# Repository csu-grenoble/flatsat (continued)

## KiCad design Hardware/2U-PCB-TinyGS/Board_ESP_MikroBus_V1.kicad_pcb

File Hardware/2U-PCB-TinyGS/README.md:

# INISAT Board for TinyGS 2.4GHz Station

This board is the firts version of the [LoRa 2.4GHz gateway](https://github.com/thingsat/tinygs_2g4station) for [TinyGS](https://tinygs.com/).

Contain Schematic and PCB file for ESP32 Vroom + 2 Mikrobus modules + 2 groves connectors (RXTX,I2C).

This Board is designed to support a ESP32 devkitC-V4 and 2 MiKroBus modules. This board is the firts version of the 2.4GHz tinygs ground station gateway and named Board_V2

The purpose of this board is to control mikrobus modules including SX1280 technology that will transmit and receive messages on a 2.4GHz radio frequency. Each module are connected to a ESP32 which will be connected to the wifi.

Mikrobus board is an add-on board socket standard made by [mikroe](https://www.mikroe.com/mikrobus)

## Pinout

Connection between ESP32 - ESP32-DevKitC V4 and Mikrobus modules

MiKroBus 0:
	 				 
	SPI_0:
	CLK 	IO18
	MISO	IO19
	MOSI	IO23
	NSS(CS)	IO05
	
	UART_0	:
	Tx	NC
	Rx	NC
	
	I2C:
	SDA	IO21
	SCL	IO22
	
	AN_0	IO33
	RESET_0 IO32
	PWM_0	IO25
	INT_0	IO26

MiKroBus 1: 				 
	
	SPI_0
	CLK 	IO18
	MISO	IO19
	MOSI	IO23
	NSS 	IO15
	
	UART_2
	Tx	IO17
	Rx	IO16
	
	I2C:
	SDA	IO21
	SCL	IO22
	
	AN_1	IO27
	RESET_1 IO14
	PWM_1	IO04
	INT_1	IO13

Grove connector available on board :

	I2C:			UART_2(Rx/Tx):		GPIO(INPUT Only):
	SDA   IO21		Tx	IO17		IO34
	SCL   IO22		Rx	IO16		IO35

UART_2 can be connected to module MiKroBus 2 or to grove connector. A jumper need to be plug to choose beetween grove output or the mikrobus module.

Two UFL connected to a SMA mount edge connector are available to plug an antenna. They are disconnected from the rest of the board, which allows to connect the module that you want to the antenna, with a SMA -UFL connector.

A powerbank can be plug under the board to supply the 3V. The [powerbank](https://www.amazon.com/Diymore-Lithium-Battery-Charging-Arduino/dp/B07SZKNST4) is design for ESP32 and is purchasable on amazon. 
5V is only available on the Mikrobus 1 module. 

Careful:
* UART0 is used for flashing and debuging. Be very careful to its use.
* GPIO grove connector are INPUT only, ESP32wroom cannot write on this connection.
* Both Chip selec (NSS) for the SPI communication are Pulled HIGH (IO05 & IO15).
* No 5V on Mikrobus 0. 

## Library and footprint

Lib & empreinte folder contains all necessary symbol and footprint for the project:
* ESP32 symbol and footprint. Footprint has been changed to match with our ESP32-devkitC-V4
* Mikrobus (mikroe-2439) symbol and footprint
* Grove connector for I2C and RxTx connection
* SMA and UFL connector

## Files

* .pro: File containing the parameters of the project.
* .sch: Schema files.
* .kicad_pcb: Printed circuit board files.
* sym-info-cache: Library list file (symbol library table): declaration of component symbol libraries available for the schema editor.
* fp-lib-table: Library list file (footprint library table): declaration of component footprint libraries available for the PCB editor.

## Contributors

* Didier DONSEZ
* [Samuel Barnola](https://www.linkedin.com/in/samuel-barnola-816354281/) ([initial design](https://github.com/thingsat/tinygs_2g4station))
* [Lucas ORLANDO BERNARDES](https://www.linkedin.com/in/lucas-orlando-bernardes-1b7397256/)

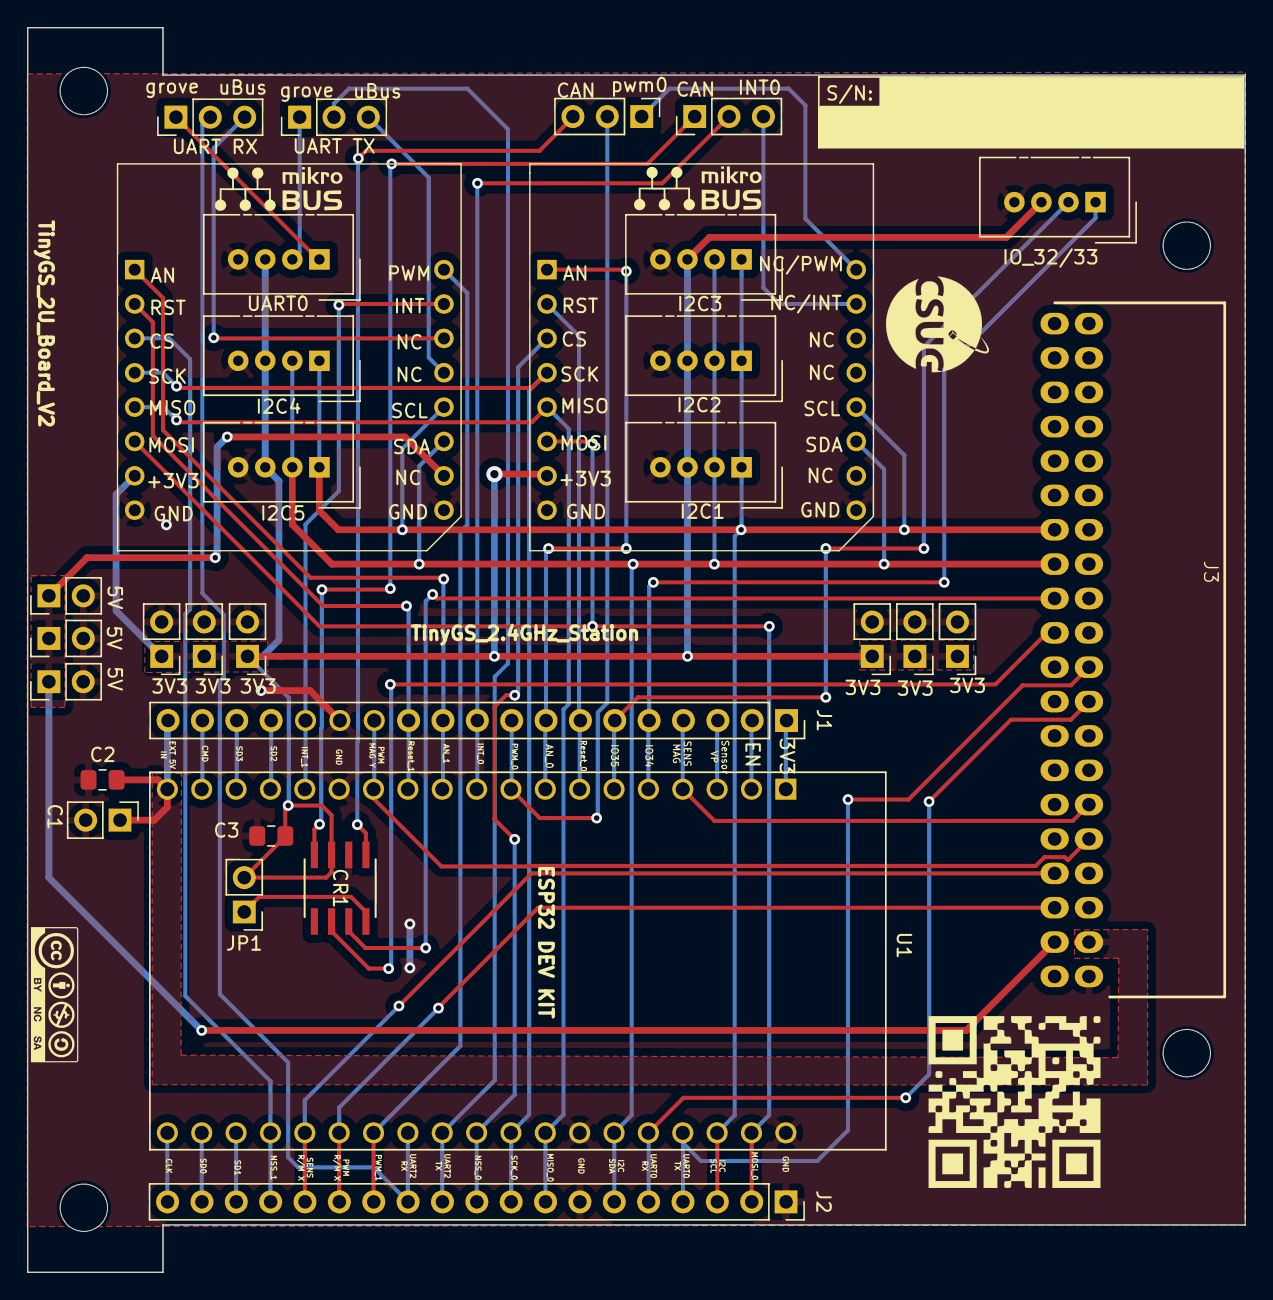
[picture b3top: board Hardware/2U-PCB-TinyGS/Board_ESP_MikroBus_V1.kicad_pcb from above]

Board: 2 copper layers, 90.0 x 92.0 mm, 31 parts (0 on the bottom side), 49 nets.

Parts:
3.1, 3.2, 3.3, 3.4, 3.5, 3.6, 5V1, 5V2, 5V3: Conn_01x02; PinHeader_1x02_P2.54mm_Vertical
C1: C; PinHeader_1x02_P2.54mm_Vertical
C2: C; C_0805_2012Metric_Pad1.18x1.45mm_HandSolder
C3: 100nF; C_0805_2012Metric_Pad1.18x1.45mm_HandSolder
CR1: L9616; SO-8_STM
I2C1, I2C2, I2C3, I2C4, I2C5: Grove; NS-Tech_Grove_1x04_P2mm_Vertical
IO_32/33: Grove; NS-Tech_Grove_1x04_P2mm_Vertical
J1, J2: Conn_01x19; PinSocket_1x19_P2.54mm_Vertical
J3: Bus Standard; flatsat_conn
JP1: Jumper_2_Open; PinHeader_1x02_P2.54mm_Vertical
Jmp_Rx1, Jmp_Rx2: Jumper_NC_Dual; PinHeader_1x03_P2.54mm_Vertical
Jmp_Tx1, Jmp_Tx2: Jumper_NC_Dual; PinHeader_1x03_P2.54mm_Vertical
MiKroBus_0, MiKroBus_1: MIKROE-924; MIKROE924
U1: ESP32-DEVKITC-32D; MODULE_ESP32-DEVKITC-32D
UART0: Grove; NS-Tech_Grove_1x04_P2mm_Vertical

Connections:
+3.3V: 3.1.1, 3.2.1, 3.3.1, 3.4.1, 3.5.1, 3.6.1, C3.1, CR1.3 (VS), I2C1.3, I2C2.3, I2C3.3, I2C4.3, I2C5.3, IO_32/33.3, J3.2 (3V3), JP1.2 (B), MiKroBus_0.7 (+3.3V), MiKroBus_1.7 (+3.3V), UART0.3
+5V: 5V1.1, 5V2.1, 5V3.1, J3.4 (5V), MiKroBus_1.15 (+5V)
/1: J1.1, U1.1 (3V3)
/2: J1.2, U1.2 (EN)
/3: J1.3, U1.3 (SENSOR_VP)
/4: J1.4, J3.11 (NC), U1.4 (SENSOR_VN)
/13: J1.13, J3.9 (NC4), U1.13 (IO12)
/16: J1.16, U1.16 (SD2)
/17: J1.17, U1.17 (SD3)
/18: J1.18, U1.18 (CMD)
/19: C1.1, C2.1, J1.19, J3.3 (V_IN), U1.19 (EXT_5V)
/33: J2.14, J3.6 (NC1), U1.33 (IO0)
/34: J2.15, J3.8 (NC3), U1.34 (IO2)
/36: J2.17, U1.36 (SD1)
/37: J2.18, U1.37 (SD0)
/38: J2.19, U1.38 (CLK)
AN_0: J1.8, MiKroBus_0.1 (AN), U1.8 (IO33)
AN_1: J1.11, MiKroBus_1.1 (AN), U1.11 (IO27)
CAN0_RD: CR1.4 (RX0), Jmp_Rx2.1
CAN0_TD: CR1.1 (TX0), Jmp_Tx2.3
CAN_RD: CR1.6 (C_L), J3.22 (RD)
CAN_TD: CR1.7 (C_H), J3.24 (TD)
ESP_CAN0_RD/INT_0: J1.10, Jmp_Rx2.2, U1.10 (IO26)
ESP_CAN0_TD/PWM_0: J1.9, Jmp_Tx2.2, U1.9 (IO25)
GNDREF: 3.1.2, 3.2.2, 3.3.2, 3.4.2, 3.5.2, 3.6.2, 5V1.2, 5V2.2, 5V3.2, C1.2, C2.2, C3.2, CR1.2 (GND), I2C1.4, I2C2.4, I2C3.4, I2C4.4, I2C5.4, IO_32/33.4, J1.14, J2.1, J2.7, J3.1 (GND), MiKroBus_0.8 (GND_1), MiKroBus_0.16 (GND_2), MiKroBus_1.8 (GND_1), MiKroBus_1.16 (GND_2), U1.14 (GND1), U1.20 (GND3), U1.26 (GND2), UART0.4
I2C_SCL: I2C1.1, I2C2.1, I2C3.1, I2C4.1, I2C5.1, J2.3, J3.28 (SCL/TX), MiKroBus_0.13 (SCL), MiKroBus_1.13 (SCL), U1.22 (IO22)
I2C_SDA: I2C1.2, I2C2.2, I2C3.2, I2C4.2, I2C5.2, J2.6, J3.26 (SDA/RX), MiKroBus_0.14 (SDA), MiKroBus_1.14 (SDA), U1.25 (IO21)
IN34: IO_32/33.1, J1.5, U1.5 (IO34)
IN35: IO_32/33.2, J1.6, U1.6 (IO35)
INT_0: Jmp_Rx2.3, MiKroBus_0.10 (INT)
INT_1: J1.15, MiKroBus_1.10 (INT), U1.15 (IO13)
MISO_0: J2.8, MiKroBus_0.5 (MISO), MiKroBus_1.5 (MISO), U1.27 (IO19)
MOSI_0: J2.2, MiKroBus_0.6 (MOSI), MiKroBus_1.6 (MOSI), U1.21 (IO23)
NSS_0: J2.10, MiKroBus_0.3 (CS), U1.29 (IO5)
NSS_1: J2.16, MiKroBus_1.3 (CS), U1.35 (IO15)
unnamed: CR1.8 (ASC), JP1.1 (A)
PWM_0: Jmp_Tx2.1, MiKroBus_0.9 (PWM)
PWM_1: J2.13, MiKroBus_1.9 (PWM), U1.32 (IO4)
Reset_0: J1.7, MiKroBus_0.2 (RST), U1.7 (IO32)
Reset_1: J1.12, MiKroBus_1.2 (RST), U1.12 (IO14)
SCK_0: J2.9, MiKroBus_0.4 (SCK), MiKroBus_1.4 (SCK), U1.28 (IO18)
UART0_Rx: J2.5, J3.17 (RX/SDA), U1.24 (RXD0)
UART0_Tx: J2.4, J3.19 (TX/SCL), U1.23 (TXD0)
UART2_Rx: J2.12, Jmp_Rx1.2, U1.31 (IO16)
UART2_Rx_MiKroBus: Jmp_Rx1.3, MiKroBus_1.11 (RX)
UART2_Rx_grove: Jmp_Rx1.1, UART0.1
UART2_Tx: J2.11, Jmp_Tx1.2, U1.30 (IO17)
UART2_Tx_MiKroBus: Jmp_Tx1.3, MiKroBus_1.12 (TX)
UART2_Tx_grove: Jmp_Tx1.1, UART0.2

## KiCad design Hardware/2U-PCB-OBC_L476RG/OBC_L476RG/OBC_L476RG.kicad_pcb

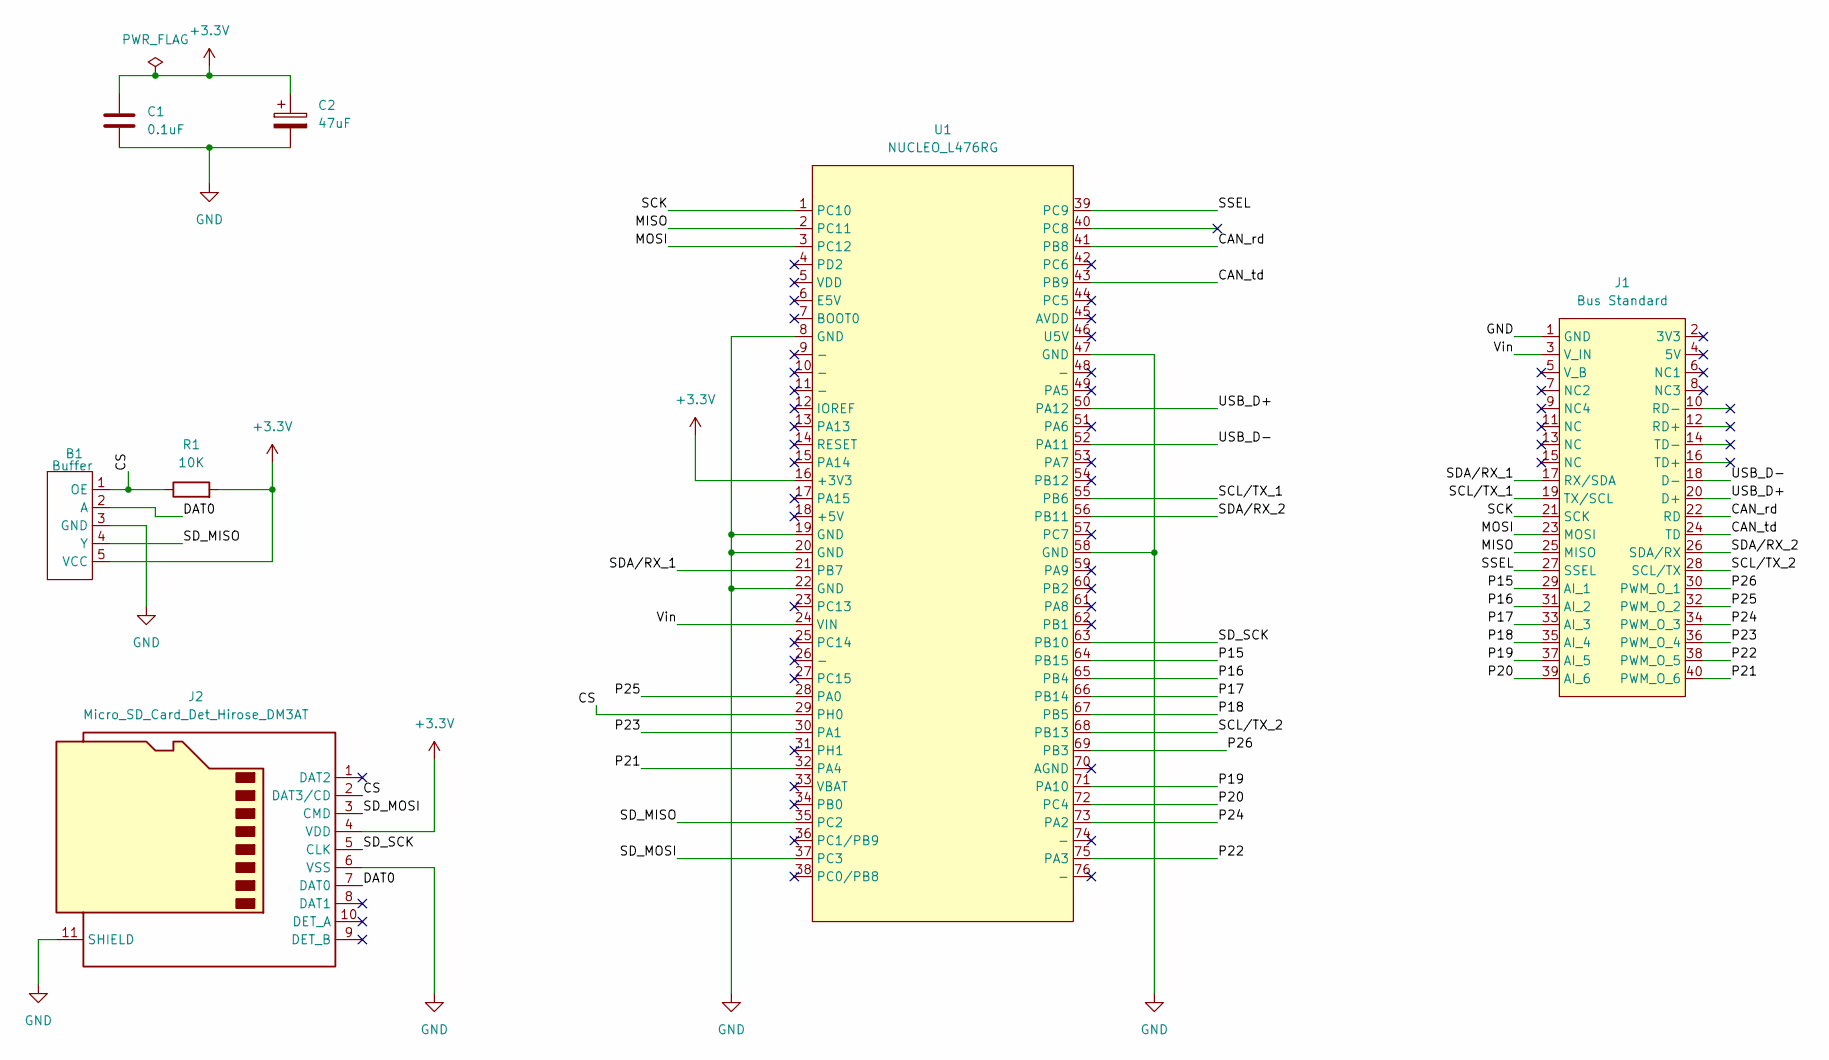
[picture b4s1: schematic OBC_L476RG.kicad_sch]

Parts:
B1: Buffer; TSOP-5_1.65x3.05mm_P0.95mm
C1: 0.1uF; C_0603_1608Metric
C2: 47uF; CP_EIA-7343-31_Kemet-D
J1: Bus Standard; flatsat_conn
J2: Micro_SD_Card_Det_Hirose_DM3AT; microSD_HC_Hirose_DM3AT-SF-PEJM5
R1: 10K; R_0805_2012Metric
U1: NUCLEO_L476RG; Nucleo64

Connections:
+3.3V: B1.5 (VCC), C1.1, C2.1, J2.4 (VDD), R1.2, U1.16 (+3V3)
/CAN_rd: J1.22 (RD), U1.41 (PB8)
/CAN_td: J1.24 (TD), U1.43 (PB9)
/CS: B1.1 (OE), J2.2 (DAT3/CD), R1.1, U1.29 (PH0)
/DAT0: B1.2 (A), J2.7 (DAT0)
/MISO: J1.25 (MISO), U1.2 (PC11)
/MOSI: J1.23 (MOSI), U1.3 (PC12)
/P15: J1.29 (AI_1), U1.64 (PB15)
/P16: J1.31 (AI_2), U1.65 (PB4)
/P17: J1.33 (AI_3), U1.66 (PB14)
/P18: J1.35 (AI_4), U1.67 (PB5)
/P19: J1.37 (AI_5), U1.71 (PA10)
/P20: J1.39 (AI_6), U1.72 (PC4)
/P21: J1.40 (PWM_O_6), U1.32 (PA4)
/P22: J1.38 (PWM_O_5), U1.75 (PA3)
/P23: J1.36 (PWM_O_4), U1.30 (PA1)
/P24: J1.34 (PWM_O_3), U1.73 (PA2)
/P25: J1.32 (PWM_O_2), U1.28 (PA0)
/P26: J1.30 (PWM_O_1), U1.69 (PB3)
/SCK: J1.21 (SCK), U1.1 (PC10)
/SCL/TX_1: J1.19 (TX/SCL), U1.55 (PB6)
/SCL/TX_2: J1.28 (SCL/TX), U1.68 (PB13)
/SDA/RX_1: J1.17 (RX/SDA), U1.21 (PB7)
/SDA/RX_2: J1.26 (SDA/RX), U1.56 (PB11)
/SD_MISO: B1.4 (Y), U1.35 (PC2)
/SD_MOSI: J2.3 (CMD), U1.37 (PC3)
/SD_SCK: J2.5 (CLK), U1.63 (PB10)
/SSEL: J1.27 (SSEL), U1.39 (PC9)
/USB_D+: J1.20 (D+), U1.50 (PA12)
/USB_D-: J1.18 (D-), U1.52 (PA11)
/Vin: J1.3 (V_IN), U1.24 (VIN)
GND: B1.3 (GND), C1.2, C2.2, J1.1 (GND), J2.6 (VSS), J2.11 (SHIELD), U1.8 (GND), U1.19 (GND), U1.20 (GND), U1.22 (GND), U1.47 (GND), U1.58 (GND)

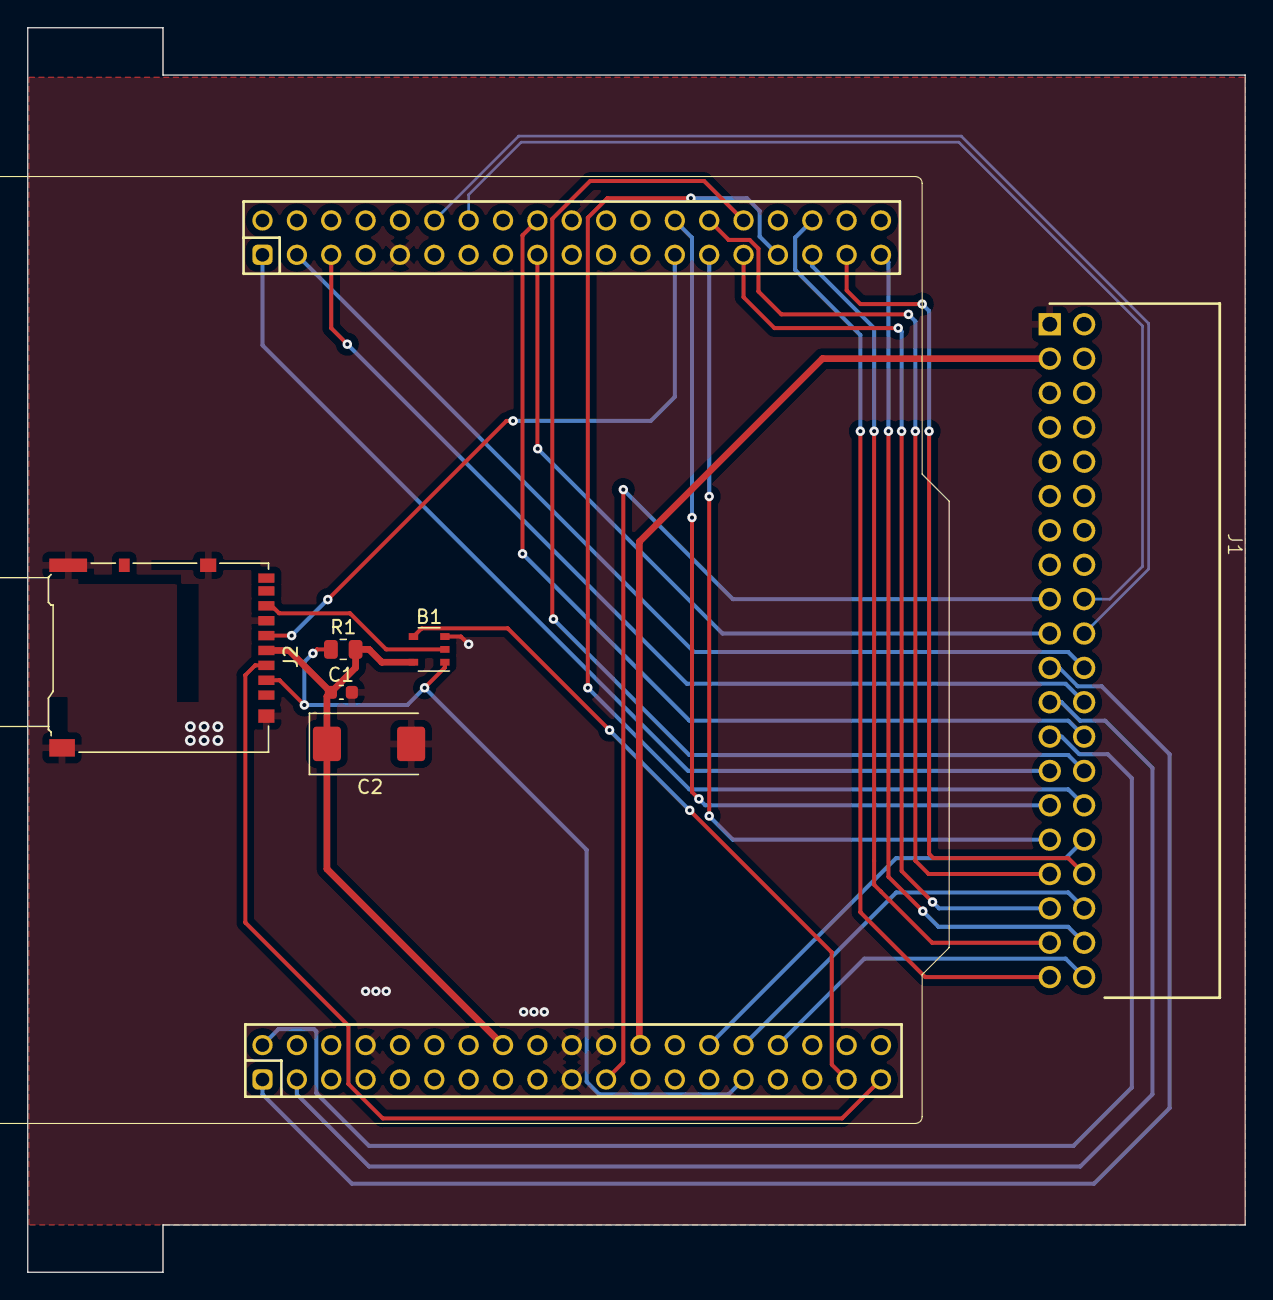
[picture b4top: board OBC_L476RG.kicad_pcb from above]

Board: 2 copper layers, 90.0 x 92.0 mm, 7 parts (0 on the bottom side), 32 nets.

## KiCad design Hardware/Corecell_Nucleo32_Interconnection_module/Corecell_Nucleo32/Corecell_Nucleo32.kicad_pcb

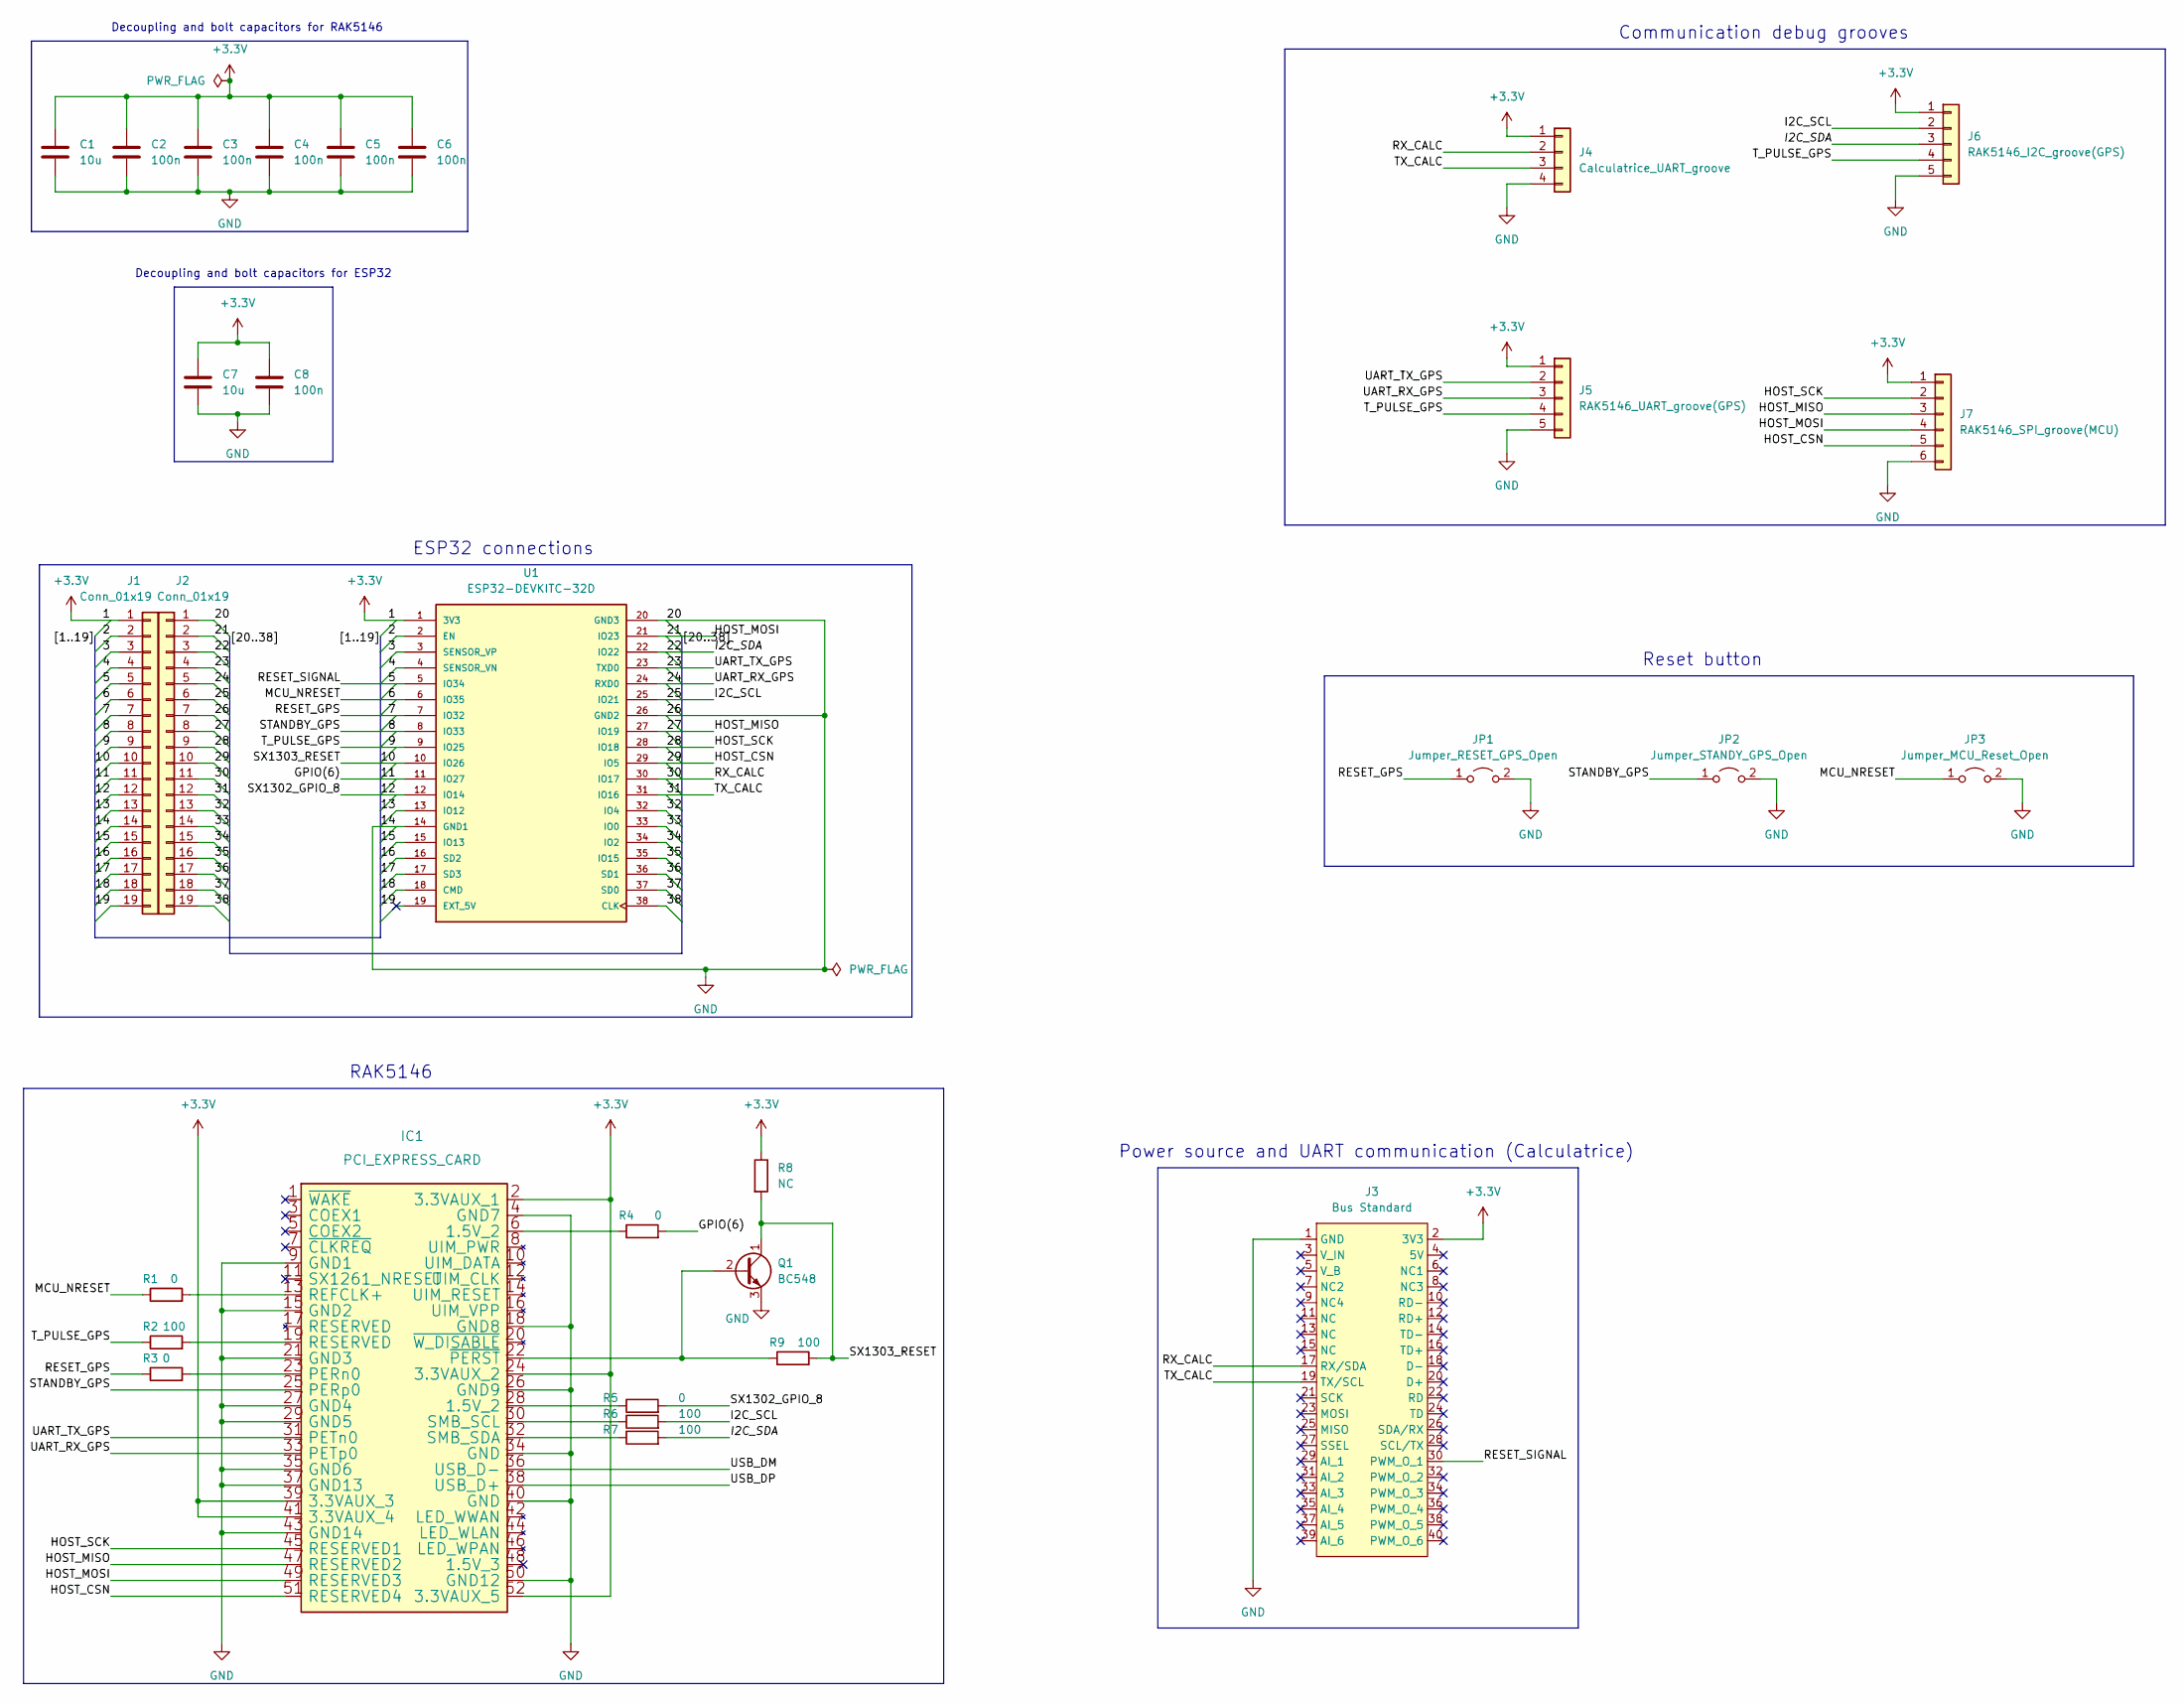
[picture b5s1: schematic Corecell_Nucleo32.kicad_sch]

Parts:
C1, C7: 10u; C_0603_1608Metric
C2, C3, C4, C5, C6, C8: 100n; C_0402_1005Metric
IC1: PCI_EXPRESS_CARD; BUS_PCI_Express_Mini
J1, J2: Conn_01x19; PinSocket_1x19_P2.54mm_Vertical
J3: Bus Standard; PinHeader_2x20_P2.54mm_Vertical
J4: Calculatrice_UART_groove; PinSocket_1x04_P2.54mm_Vertical
J5: RAK5146_UART_groove(GPS); PinSocket_1x05_P2.54mm_Vertical
J6: RAK5146_I2C_groove(GPS); PinSocket_1x05_P2.54mm_Vertical
J7: RAK5146_SPI_groove(MCU); PinSocket_1x06_P2.54mm_Vertical
JP1: Jumper_RESET_GPS_Open; SW_Push_1P1T_NO_CK_KMR2
JP2: Jumper_STANDY_GPS_Open; SW_Push_1P1T_NO_CK_KMR2
JP3: Jumper_MCU_Reset_Open; SW_Push_1P1T_NO_CK_KMR2
Q1: BC548; TO-92_Inline
R1, R3, R4, R5: 0; R_0402_1005Metric
R2, R6, R7, R9: 100; R_0402_1005Metric
R8: NC; R_0402_1005Metric
U1: ESP32-DEVKITC-32D; MODULE_ESP32-DEVKITC-32D; PARTREV 4

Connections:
+3V3: C1.1, C2.1, C3.1, C4.1, C5.1, C6.1, C7.1, C8.1, IC1.2 (3.3VAUX_1), IC1.24 (3.3VAUX_2), IC1.39 (3.3VAUX_3), IC1.41 (3.3VAUX_4), IC1.52 (3.3VAUX_5), J1.1, J3.2 (3V3), J4.1, J5.1, J6.1, J7.1, R8.1, U1.1 (3V3)
/2: J1.2, U1.2 (EN)
/3: J1.3, U1.3 (SENSOR_VP)
/4: J1.4, U1.4 (SENSOR_VN)
/5: J1.5, J3.30 (PWM_O_1), U1.5 (IO34)
/6: J1.6, JP3.1 (A), R1.1, U1.6 (IO35)
/7: J1.7, JP1.1 (A), R3.1, U1.7 (IO32)
/8: IC1.25 (PERp0), J1.8, JP2.1 (A), U1.8 (IO33)
/9: J1.9, J5.4, J6.4, R2.1, U1.9 (IO25)
/10: J1.10, Q1.1 (C), R8.2, R9.2, U1.10 (IO26)
/11: J1.11, R4.2, U1.11 (IO27)
/12: J1.12, R5.2, U1.12 (IO14)
/13: J1.13, U1.13 (IO12)
/15: J1.15, U1.15 (IO13)
/16: J1.16, U1.16 (SD2)
/17: J1.17, U1.17 (SD3)
/18: J1.18, U1.18 (CMD)
/19: J1.19, U1.19 (EXT_5V)
/21: IC1.49 (RESERVED3), J2.2, J7.4, U1.21 (IO23)
/22: J2.3, J6.3, R7.2, U1.22 (IO22)
/23: IC1.31 (PETn0), J2.4, J5.2, U1.23 (TXD0)
/24: IC1.33 (PETp0), J2.5, J5.3, U1.24 (RXD0)
/25: J2.6, J6.2, R6.2, U1.25 (IO21)
/27: IC1.47 (RESERVED2), J2.8, J7.3, U1.27 (IO19)
/28: IC1.45 (RESERVED1), J2.9, J7.2, U1.28 (IO18)
/29: IC1.51 (RESERVED4), J2.10, J7.5, U1.29 (IO5)
/30: J2.11, J3.17 (RX/SDA), J4.2, U1.30 (IO17)
/31: J2.12, J3.19 (TX/SCL), J4.3, U1.31 (IO16)
/32: J2.13, U1.32 (IO4)
/33: J2.14, U1.33 (IO0)
/34: J2.15, U1.34 (IO2)
/35: J2.16, U1.35 (IO15)
/36: J2.17, U1.36 (SD1)
/37: J2.18, U1.37 (SD0)
/38: J2.19, U1.38 (CLK)
/USB_DM: IC1.36 (USB_D-)
/USB_DP: IC1.38 (USB_D+)
GND: C1.2, C2.2, C3.2, C4.2, C5.2, C6.2, C7.2, C8.2, IC1.4 (GND7), IC1.9 (GND1), IC1.15 (GND2), IC1.18 (GND8), IC1.21 (GND3), IC1.26 (GND9), IC1.27 (GND4), IC1.29 (GND5), IC1.34 (GND), IC1.35 (GND6), IC1.37 (GND13), IC1.40 (GND), IC1.43 (GND14), IC1.50 (GND12), J1.14, J2.1, J2.7, J3.1 (GND), J4.4, J5.5, J6.5, J7.6, JP1.2 (B), JP2.2 (B), JP3.2 (B), Q1.3 (E), U1.14 (GND1), U1.20 (GND3), U1.26 (GND2)
unnamed: IC1.6 (1.5V_2), R4.1
unnamed: IC1.13 (REFCLK+), R1.2
unnamed: IC1.19 (RESERVED), R2.2
unnamed: IC1.22 (~PERST), Q1.2 (B), R9.1
unnamed: IC1.23 (PERn0), R3.2
unnamed: IC1.28 (1.5V_2), R5.1
unnamed: IC1.30 (SMB_SCL), R6.1
unnamed: IC1.32 (SMB_SDA), R7.1

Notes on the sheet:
RAK5146
Decoupling and bolt capacitors for ESP32
ESP32 connections
Power source and UART communication (Calculatrice)
Communication debug grooves
Reset button
Decoupling and bolt capacitors for RAK5146

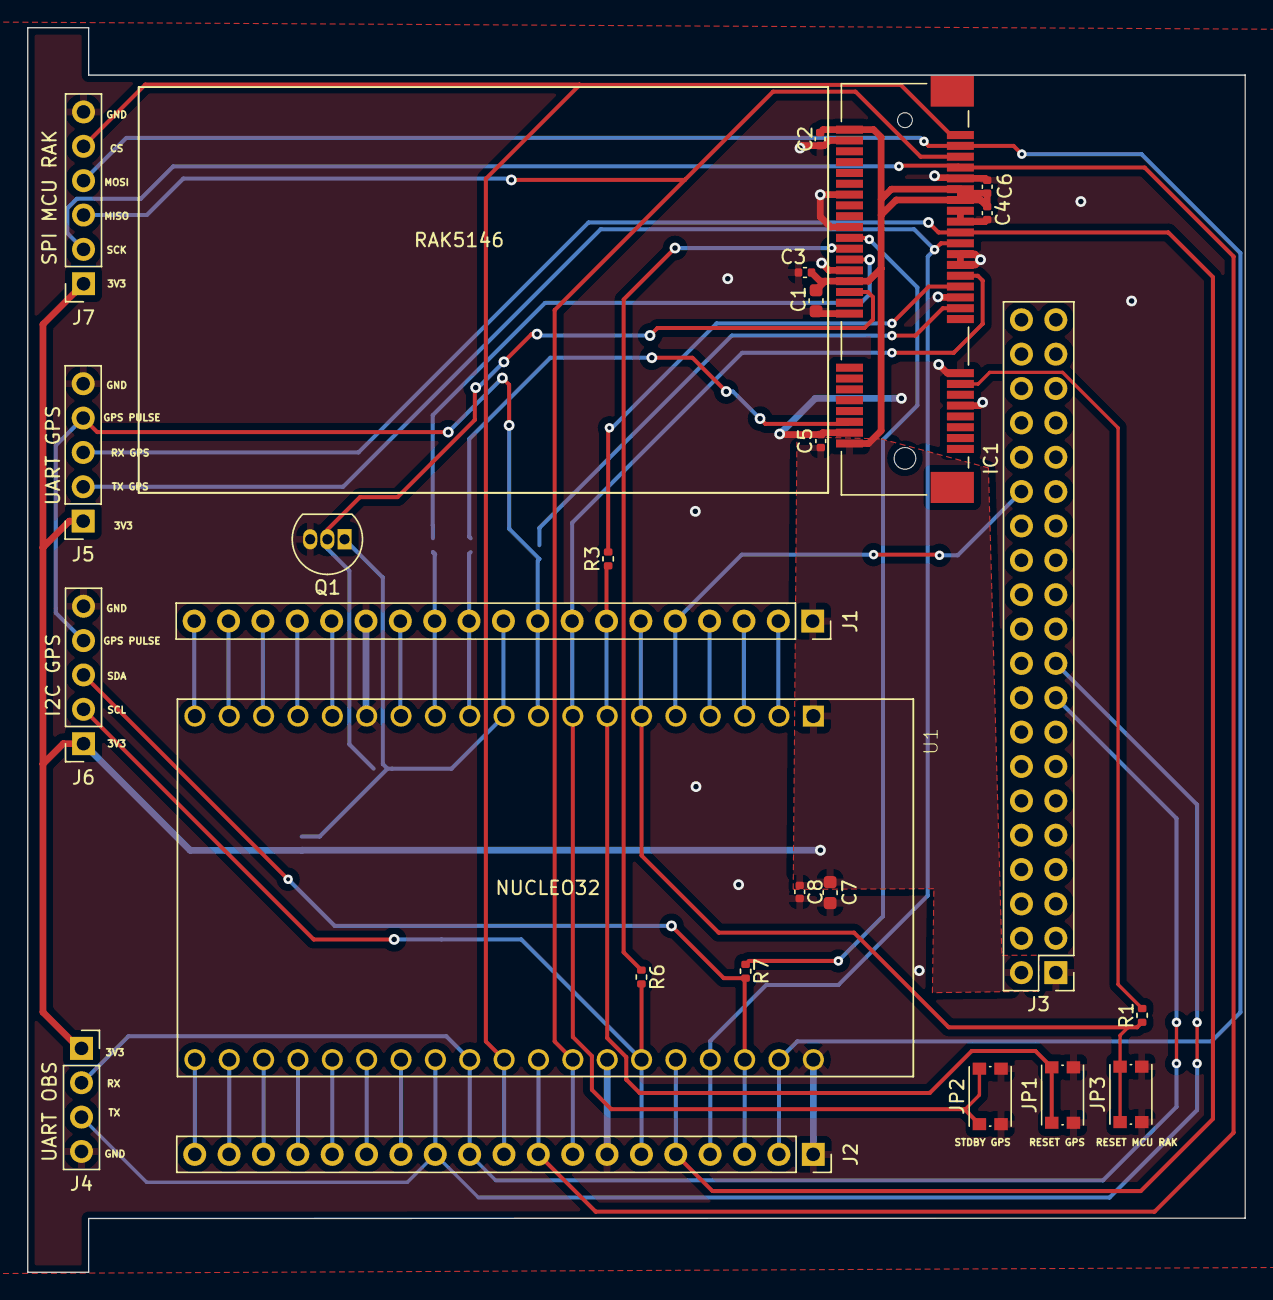
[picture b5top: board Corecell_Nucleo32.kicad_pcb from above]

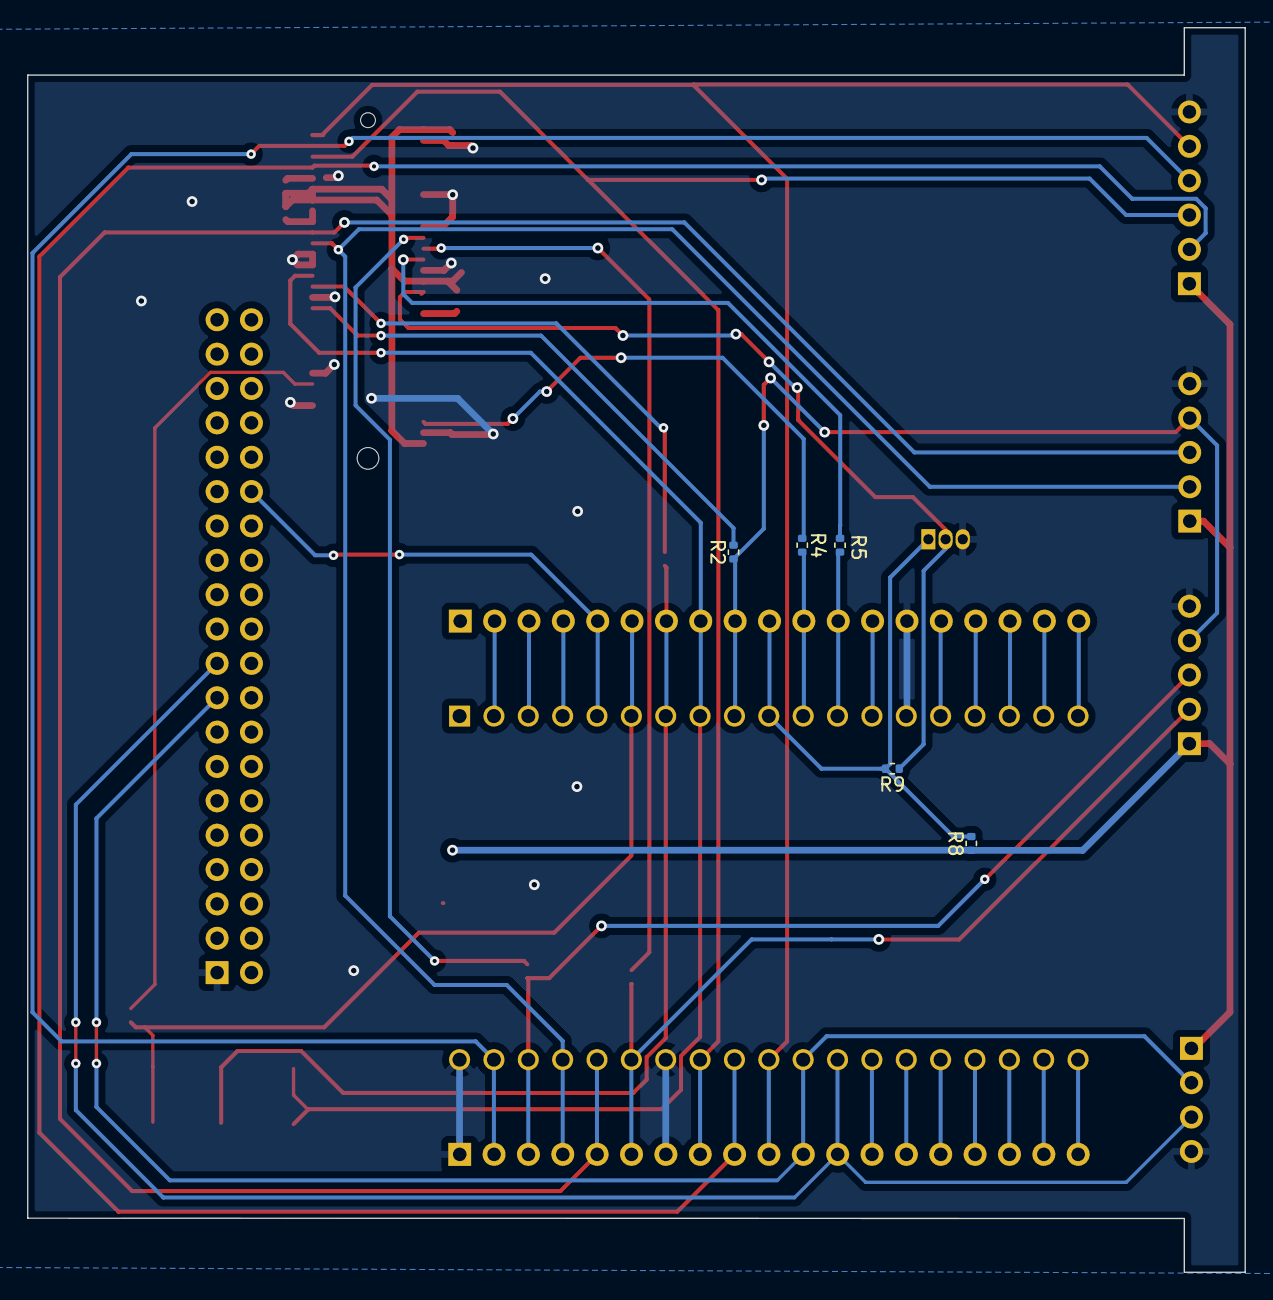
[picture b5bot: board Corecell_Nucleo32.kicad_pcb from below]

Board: 2 copper layers, 90.0 x 92.0 mm, 30 parts (5 on the bottom side), 44 nets.
